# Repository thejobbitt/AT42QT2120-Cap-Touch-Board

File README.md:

# AT42QT2120-Cap-Touch-Board

I2C 12 input basic board design. Uses the SOIC package and 1206 resistors and caps.

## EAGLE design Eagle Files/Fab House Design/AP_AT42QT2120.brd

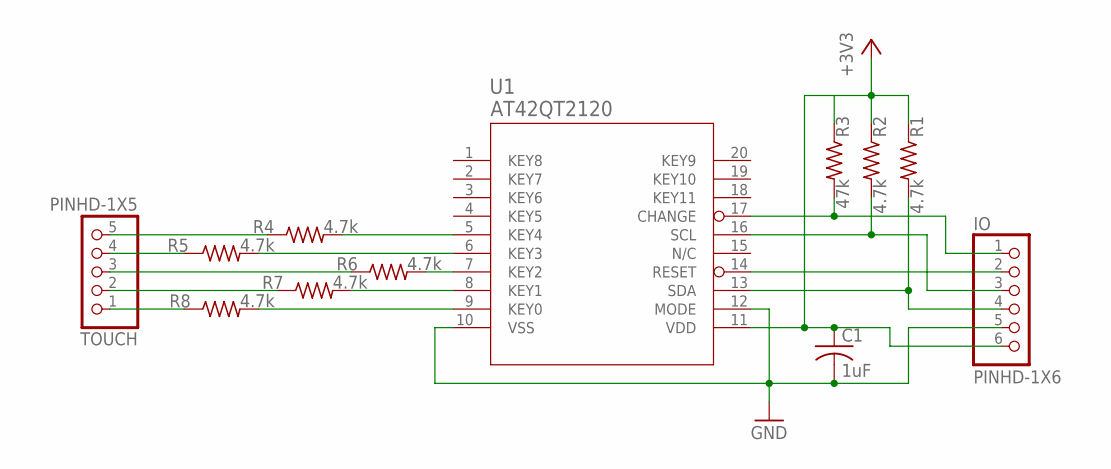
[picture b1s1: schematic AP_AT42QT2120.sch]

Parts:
C1: 1uF; C1206
IO: PINHD-1X6; 1X06
R1, R2, R4, R5, R6, R7, R8: 4.7k; R1206
R3: 47k; R1206
TOUCH: PINHD-1X5; 1X05
U1: AT42QT2120; SOIC20

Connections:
+3V3: C1.1, IO.6, R1.1, R2.1, R3.1, U1.11 (VDD)
GND: C1.2, IO.5, U1.10 (VSS), U1.12 (MODE)
unnamed: IO.2, U1.14 (RESET)
unnamed: R5.1, TOUCH.4
unnamed: R4.2, U1.5 (KEY4)
unnamed: R5.2, U1.6 (KEY3)
unnamed: R6.2, U1.7 (KEY2)
unnamed: R7.2, U1.8 (KEY1)
unnamed: R8.2, U1.9 (KEY0)
unnamed: R8.1, TOUCH.1
unnamed: R7.1, TOUCH.2
unnamed: R6.1, TOUCH.3
unnamed: R4.1, TOUCH.5
unnamed: IO.3, R2.2, U1.16 (SCL)
unnamed: IO.1, R3.2, U1.17 (CHANGE)
unnamed: IO.4, R1.2, U1.13 (SDA)

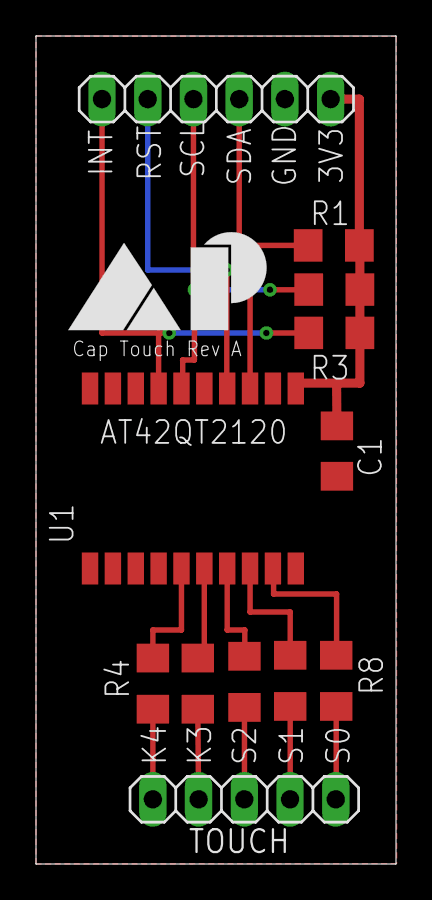
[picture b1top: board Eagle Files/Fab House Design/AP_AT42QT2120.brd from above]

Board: 2 copper layers, 20.0 x 46.0 mm, 12 parts (0 on the bottom side), 16 nets.

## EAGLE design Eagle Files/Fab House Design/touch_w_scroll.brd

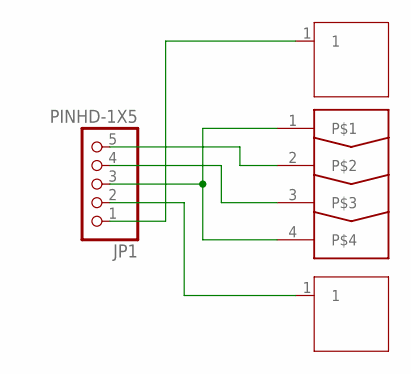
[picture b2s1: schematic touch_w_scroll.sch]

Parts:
JP1: PINHD-1X5; 1X05
U$1: SLIDE_PAD; SLIDE
U$2: 12X12_PAD
U$4: 12X12_PADLED; 12X12_PAD_LED

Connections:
unnamed: JP1.1, U$2.1
unnamed: JP1.2, U$4.1
unnamed: JP1.3, U$1.1, U$1.4
unnamed: JP1.4, U$1.3
unnamed: JP1.5, U$1.2

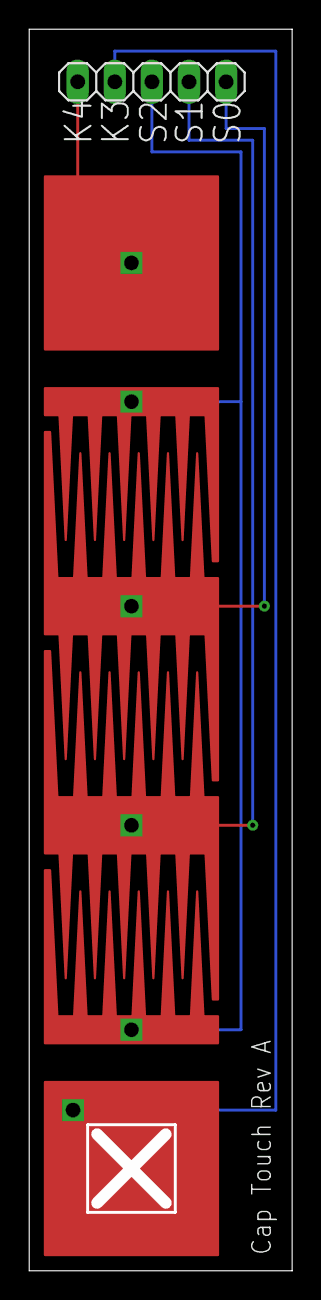
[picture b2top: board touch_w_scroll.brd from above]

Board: 2 copper layers, 17.2 x 84.2 mm, 4 parts (0 on the bottom side), 5 nets.

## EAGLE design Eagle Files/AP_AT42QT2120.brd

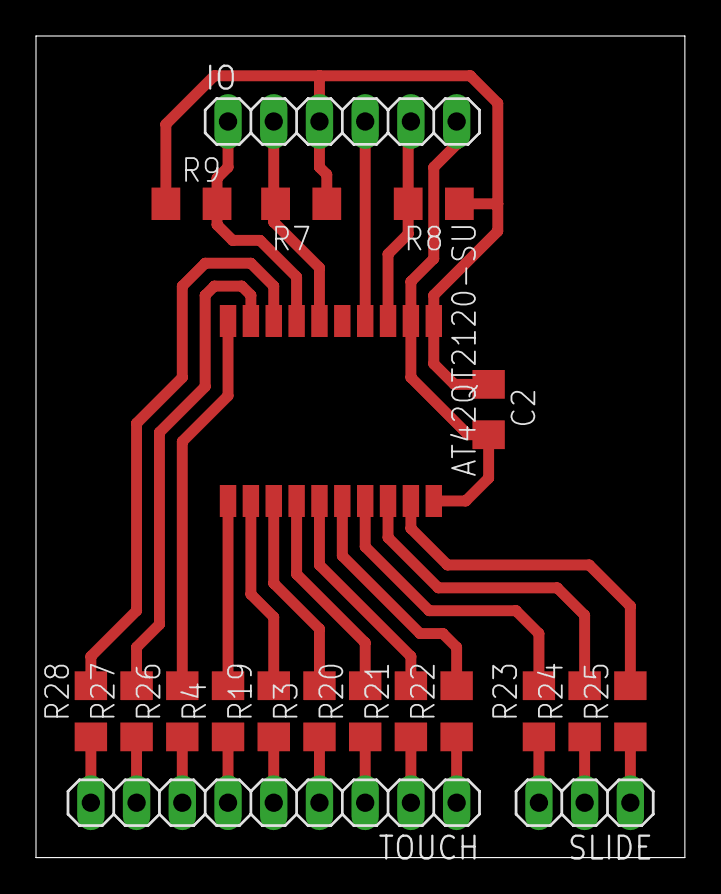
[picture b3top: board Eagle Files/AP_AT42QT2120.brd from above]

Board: 2 copper layers, 36.0 x 45.6 mm, 20 parts (0 on the bottom side), 30 nets.

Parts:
C2: 1uF; C1206
IO: PINHD-1X6; 1X06
R3, R4, R7, R8, R19, R20, R21, R22, R23, R24, R25, R26, R27, R28: 4.7k; R1206
R9: 47k; R1206
SLIDE: PINHD-1X3; 1X03
TOUCH: PINHD-1X9; 1X09
U$1: AT42QT2120-SU; SOIC20

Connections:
+3V3: C2.1, IO.3, R7.1, R8.1, R9.1, U$1.11
GND: C2.2, IO.6, U$1.10, U$1.12
unnamed: R4.2, U$1.1
unnamed: R19.2, U$1.2
unnamed: R3.2, U$1.3
unnamed: R20.2, U$1.4
unnamed: R21.2, U$1.5
unnamed: R22.2, U$1.6
unnamed: R23.2, U$1.7
unnamed: R24.2, U$1.8
unnamed: R25.2, U$1.9
unnamed: R25.1, SLIDE.1
unnamed: R24.1, SLIDE.2
unnamed: R23.1, SLIDE.3
unnamed: R22.1, TOUCH.1
unnamed: R21.1, TOUCH.2
unnamed: R20.1, TOUCH.3
unnamed: R3.1, TOUCH.4
unnamed: R19.1, TOUCH.5
unnamed: R4.1, TOUCH.6
unnamed: R26.1, TOUCH.7
unnamed: R26.2, U$1.20
unnamed: R27.1, TOUCH.8
unnamed: R28.1, TOUCH.9
unnamed: R27.2, U$1.19
unnamed: IO.2, R7.2, U$1.16
unnamed: IO.1, R9.2, U$1.17
unnamed: IO.5, R8.2, U$1.13
unnamed: IO.4, U$1.14
unnamed: R28.2, U$1.18

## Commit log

2022-04-04 v2 with larger packages
2022-04-05 pcb changes
2022-04-05 touch pcb started
2022-04-06 added x profile
2022-04-06 maybe final touch board
2022-04-06 drill
2022-06-20 New folder structure
2022-06-20 pushhhhh
2022-06-21 board tags
2022-06-21 finals

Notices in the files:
parts and their libraries:
2022-03-29_19-48-10_Library: COPYRIGHT: Copyright (C) 2022 Ultra Librarian. All rights reserved.
